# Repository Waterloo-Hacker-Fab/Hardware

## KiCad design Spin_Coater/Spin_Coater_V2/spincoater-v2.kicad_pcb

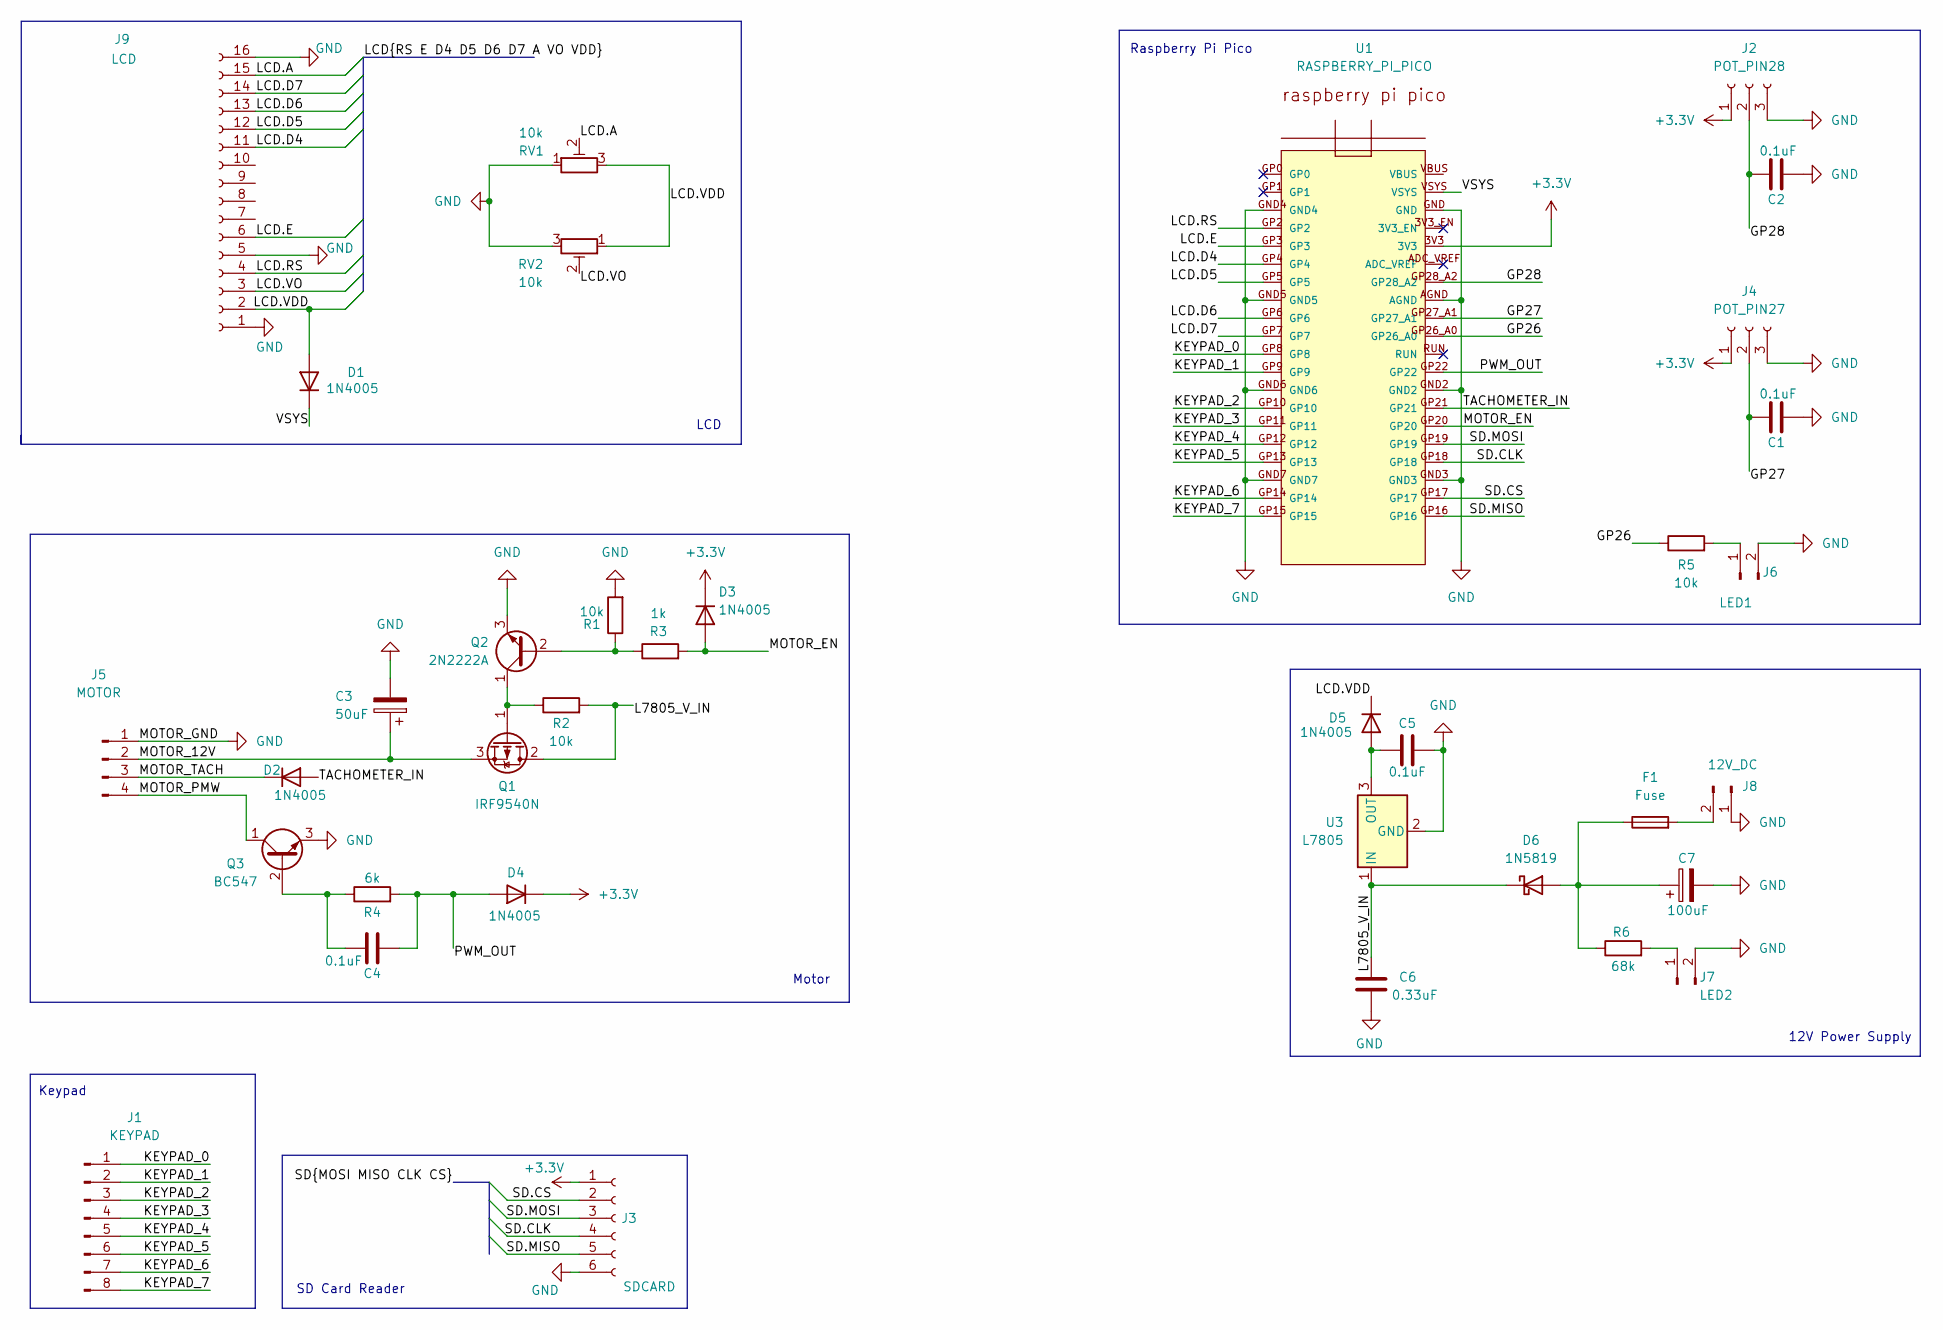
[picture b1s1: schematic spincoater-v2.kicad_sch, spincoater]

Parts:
C1, C2, C4, C5: 0.1uF; C_0603_1608Metric_Pad1.08x0.95mm_HandSolder
C3: 50uF; CP_Radial_D13.0mm_P5.00mm
C6: 0.33uF; C_0603_1608Metric_Pad1.08x0.95mm_HandSolder
C7: 100uF; CP_Radial_D13.0mm_P5.00mm
D1, D2, D3, D4, D5: 1N4005; D_DO-41_SOD81_P10.16mm_Horizontal
D6: 1N5819; D_DO-41_SOD81_P10.16mm_Horizontal
F1: Fuse; Fuseholder_Keystone_3555-2
J1: KEYPAD; PinSocket_1x08_P2.54mm_Vertical
J2: POT_PIN28; PinSocket_1x03_P2.54mm_Vertical
J3: SDCARD; PinSocket_1x06_P2.54mm_Vertical
J4: POT_PIN27; PinSocket_1x03_P2.54mm_Vertical
J5: MOTOR; PinHeader_1x04_P2.54mm_Vertical
J6: LED1; PinHeader_1x02_P2.54mm_Vertical
J7: LED2; PinHeader_1x02_P2.54mm_Vertical
J8: 12V_DC; PinHeader_1x02_P2.54mm_Vertical
J9: LCD; PinSocket_1x16_P2.54mm_Vertical
Q1: IRF9540N; TO-220-3_Horizontal_TabUp
Q2: 2N2222A; TO-92_Inline_Horizontal1
Q3: BC547; TO-92_Inline_Horizontal1
R1, R2, R5: 10k; R_0603_1608Metric_Pad0.98x0.95mm_HandSolder
R3: 1k; R_0603_1608Metric_Pad0.98x0.95mm_HandSolder
R4: 6k; R_0603_1608Metric_Pad0.98x0.95mm_HandSolder
R6: 68k; R_0603_1608Metric_Pad0.98x0.95mm_HandSolder
RV1, RV2: 10k; Potentiometer_Vishay_T93YA_Vertical
U1: RASPBERRY_PI_PICO; RPI_PICO
U3: L7805; TO-220-3_Horizontal_TabUp

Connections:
+3.3V: D3.1 (K), D4.1 (K), J2.1, J3.1, J4.1, U1.3V3
/GP26: R5.1, U1.GP26_A0
/GP27: C1.1, J4.2, U1.GP27_A1
/GP28: C2.1, J2.2, U1.GP28_A2
/KEYPAD_0: J1.1, U1.GP8
/KEYPAD_1: J1.2, U1.GP9
/KEYPAD_2: J1.3, U1.GP10
/KEYPAD_3: J1.4, U1.GP11
/KEYPAD_4: J1.5, U1.GP12
/KEYPAD_5: J1.6, U1.GP13
/KEYPAD_6: J1.7, U1.GP14
/KEYPAD_7: J1.8, U1.GP15
/L7805_V_IN: C6.2, D6.1 (K), Q1.2 (D), R2.2, U3.1 (IN)
/LCD.A: J9.15, RV1.2
/LCD.D4: J9.11, U1.GP4
/LCD.D5: J9.12, U1.GP5
/LCD.D6: J9.13, U1.GP6
/LCD.D7: J9.14, U1.GP7
/LCD.E: J9.6, U1.GP3
/LCD.RS: J9.4, U1.GP2
/LCD.VDD: D1.2 (A), D5.1 (K), J9.2, RV1.3, RV2.1
/LCD.VO: J9.3, RV2.2
/MOTOR_12V: C3.1, J5.2, Q1.3 (S)
/MOTOR_EN: D3.2 (A), R3.2, U1.GP20
/MOTOR_PMW: J5.4, Q3.1 (C)
/MOTOR_TACH: D2.1 (K), J5.3
/PWM_OUT: C4.2, D4.2 (A), R4.2, U1.GP22
/SD.CLK: J3.4, U1.GP18
/SD.CS: J3.2, U1.GP17
/SD.MISO: J3.5, U1.GP16
/SD.MOSI: J3.3, U1.GP19
/TACHOMETER_IN: D2.2 (A), U1.GP21
/VSYS: D1.1 (K), U1.VSYS
GND: C1.2, C2.2, C3.2, C5.2, C6.1, C7.2, J2.3, J3.6, J4.3, J5.1, J6.2, J7.2, J8.1, J9.1, J9.5, J9.16, Q2.3 (E), Q3.3 (E), R1.2, RV1.1, RV2.3, U1.AGND, U1.GND, U1.GND2, U1.GND3, U1.GND4, U1.GND5, U1.GND6, U1.GND7, U3.2 (GND)
unnamed: C5.1, D5.2 (A), U3.3 (OUT)
unnamed: C7.1, D6.2 (A), F1.1, R6.1
unnamed: J6.1, R5.2
unnamed: J7.1, R6.2
unnamed: F1.2, J8.2
unnamed: Q1.1 (G), Q2.1 (C), R2.1
unnamed: Q2.2 (B), R1.1, R3.1
unnamed: C4.1, Q3.2 (B), R4.1

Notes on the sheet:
Keypad
SD Card Reader
Motor
LCD
12V Power Supply
Raspberry Pi Pico

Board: 2 copper layers, 36 parts (0 on the bottom side), 42 nets, no tracks yet.

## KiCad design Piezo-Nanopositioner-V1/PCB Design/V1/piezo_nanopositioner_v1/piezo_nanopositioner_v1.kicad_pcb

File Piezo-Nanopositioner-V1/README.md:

# Piezo Stage 

## Overview
This is an open source piezo stage build, heavily inspired by the following paper: https://www.sciencedirect.com/science/article/pii/S2468067222000621

Notes about the paper mentioned above: 
1. The paper provides a great schematic for a piezo driver PCB. However, some of the parts are obsolete, and the design is built on a perfboard.

2. The paper also includes CAD design files. However, the mechanical parts used in these designs are either difficult to source or obsolete. In our design, we decided to replace these hard-to-get parts with alternatives based on CMU’s current stage. The CAD files require no modification when used with the current BOM.

The goal of the PCB redesign was to: 
1. Remove obsolete components -  Easier to source parts and ensures long-term availability.

2. Remove perfboard design - Simplifies the assembly process.

The goal of the CAD redesign was to: 
1. Modular attachment system - Allows mounting the stage to various surfaces (e.g., metric/imperial optical breadboard).

2. Modular mounting surface - Enables testing of different wafer clamping systems.

3. Up-to-date 3D printable CAD files - No obsolete parts, uses current BOM

4. Provide a "standard" stage - Provide a "base" so people can build on top of (incorporating measurement systems or custom wafer clamps.).

5. Provide a cheaper alternative for building a piezo stage.

---

## Folder Structure

- **/CAD Design/**  
  Contains all the .sldprt/.sldasm/.stl files needed to print/modify for your needs.  
  <span style="color:red"> Note: Contains BOM for the piezo stage build ("MECH_piezo_stage_BOM.xlsx") </span>

- **/LTspice Simulation/**  
  Nitty gritty simulations of schematics (good for learning, useless for recreating the project).

- **/PCB Design/**  
  PCB design files (Gerber and drill files) for the XYZ Piezo Stage driver. Also comes with KiCAD files.  
  <span style="color:red"> Note: Contains BOM for the piezo stage PCB ("PCB_piezo_stage_BOM.csv") </span>

- **/Pictures/**  
  Pictures of the PCB and mechanical parts.

- **/Firmware/**  
  Coming soon.

---

## 3D Printing

- List of parts to print (Check "Printed Parts" folder):  
  - `XY_Base.SLDPRT` — Base frame for both X & Y stage (Print 2 for XY stage.)  
  - `XY_Plate.SLDPRT` — Top plate for both X & Y stage (Print 2 for XY stage.)
  - `Z_Base.SLDPRT` — Base frame for Z stage (print only 1 for XYZ stage.)  
  - `Z_Plate.SLDPRT` — Top plate for Z stage (print only 1 for XYZ stage.)
  - `Z_Cover.SLDPRT` — Side cover frame for Z stage (print only 1 for XYZ stage.)

  Optional:
  - `XY_Base_Connector_(Metric).SLDPRT` — Connector for mounting the stage to a metric optical breadboard (print only 1.)
  - `XY_Base_Connector_(Imperial).SLDPRT` — Coming soon.

- Printing recommendations:  
  - Material: PLA or ABS  
  - Layer height: 0.2 mm  
  - Infill: 20% (adjust for strength as needed)  
  - Supports: Required for all parts.

---

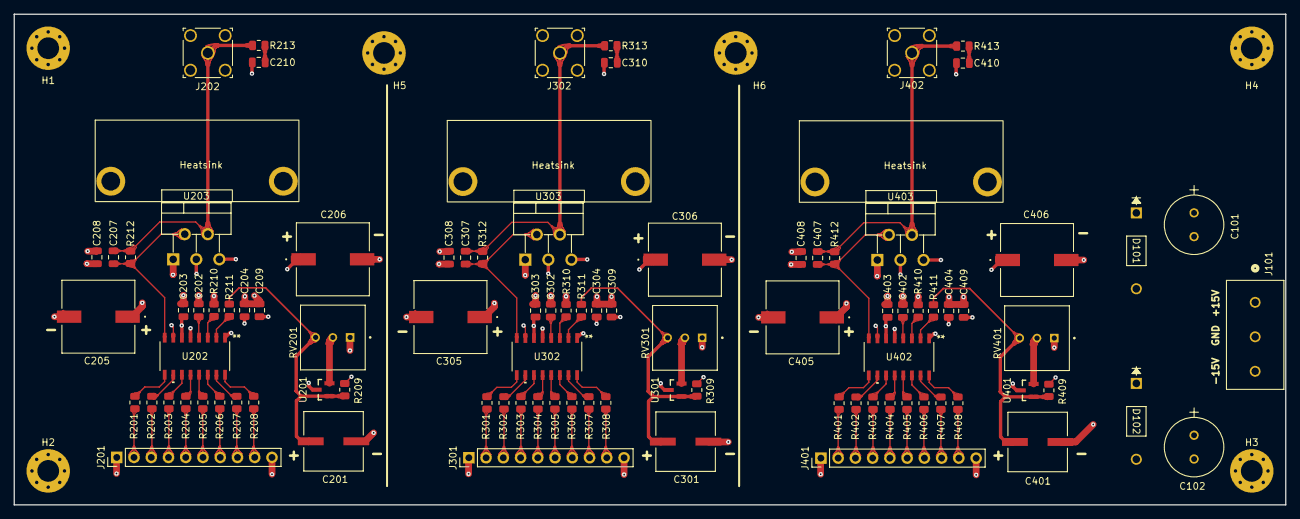
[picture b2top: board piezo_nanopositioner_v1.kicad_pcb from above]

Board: 4 copper layers, 187.2 x 72.2 mm, 101 parts (0 on the bottom side), 27 nets.

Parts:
C101, C102: 100uF 50V; CAP_YX_8X11P5_RUB
C201, C301, C401: 47u; CAP_EEFC_E_PAN
C202, C302, C402: 10n; C_0805_2012Metric
C203, C204, C208, C209, C303, C304, C308, C309, C403, C404, C408, C409: 100n; C_0805_2012Metric
C205, C206, C305, C306, C405, C406: 470u; CAP_ZSU_G12_PAN
C207, C307, C407: 68p; C_0805_2012Metric
C210, C310, C410: 4.7n; C_0805_2012Metric
D101, D102: D; DO-41_DIO
H1, H2, H3, H4, H5, H6: MountingHole; MountingHole_3.2mm_M3_Pad_Via
Heatsink: V6560Y
Heatsink#2, Heatsink#3: V6560Y
J101: Conn_01x03_Pin; CONN_39880-0303_MOL
J201, J301, J401: Conn_01x10_Pin; PinHeader_1x10_P2.54mm_Vertical
J202, J302, J402: RF2-04A-T-00-50-G; CONN_RF2-04A-T-00-50-G_ADM
R201, R202, R203, R204, R205, R206, R207, R208, R301, R302, R303, R304, R305, R306, R307, R308, R401, R402, R403, R404, R405, R406, R407, R408: 100R; R_0805_2012Metric
R209, R309, R409: 1k; R_0805_2012Metric
R210, R211, R310, R311, R410, R411: 5k; R_0805_2012Metric
R212, R312, R412: 15k; R_0805_2012Metric
R213, R313, R413: 10R; R_0805_2012Metric
RV201, RV301, RV401: 10k; TRIM_COM-09806
U201, U301, U401: TL431AIDBZR; DBZ0003A_N
U202, U302, U402: DAC0800LCM; M16A_TEX
U203, U303, U403: TDA2050; TO-220-5_P3.4x3.7mm_StaggerOdd_Lead3.8mm_Vertical

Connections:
+15V: C101.1, C204.2, C206.1, C209.1, C304.2, C306.1, C309.1, C404.2, C406.1, C409.1, D101.1 (K), J101.1, R209.1, R309.1, R409.1, U202.1 (V+), U203.5 (+Vs), U302.1 (V+), U303.5 (+Vs), U402.1 (V+), U403.5 (+Vs)
-15V: C102.2, C202.2, C203.1, C205.2, C208.2, C302.2, C303.1, C305.2, C308.2, C402.2, C403.1, C405.2, C408.2, D102.2 (A), J101.3, U202.7 (V-), U203.3 (-Vs), U302.7 (V-), U303.3 (-Vs), U402.7 (V-), U403.3 (-Vs)
/Z_DAC/VRef+: C201.1, C301.1, C401.1, R209.2, R211.2, R309.2, R311.2, R409.2, R411.2, RV201.3, RV301.3, RV401.3, U201.1 (c), U301.1 (c), U401.1 (c)
GND: C101.2, C102.1, C201.2, C203.2, C204.1, C205.1, C206.2, C208.1, C209.2, C210.2, C301.2, C303.2, C304.1, C305.1, C306.2, C308.1, C309.2, C310.2, C401.2, C403.2, C404.1, C405.1, C406.2, C408.1, C409.2, C410.2, D101.2 (A), D102.1 (K), J101.2, J201.1, J201.10, J202.2, J202.3, J202.4, J202.5, J301.1, J301.10, J302.2, J302.3, J302.4, J302.5, J401.1, J401.10, J402.2, J402.3, J402.4, J402.5, R210.2, R310.2, R410.2, RV201.1, RV301.1, RV401.1, U201.3 (a), U202.5 (VLC), U202.6 (~IOUT), U203.1 (+), U301.3 (a), U302.5 (VLC), U302.6 (~IOUT), U303.1 (+), U401.3 (a), U402.5 (VLC), U402.6 (~IOUT), U403.1 (+)
unnamed: C210.1, C310.1, C410.1, R213.2, R313.2, R413.2
unnamed: J201.2, J301.2, J401.2, R201.1, R301.1, R401.1
unnamed: J201.3, J301.3, J401.3, R202.1, R302.1, R402.1
unnamed: J201.4, J301.4, J401.4, R203.1, R303.1, R403.1
unnamed: J201.5, J301.5, J401.5, R204.1, R304.1, R404.1
unnamed: J201.6, J301.6, J401.6, R205.1, R305.1, R405.1
unnamed: J201.7, J301.7, J401.7, R206.1, R306.1, R406.1
unnamed: J201.8, J301.8, J401.8, R207.1, R307.1, R407.1
unnamed: J201.9, J301.9, J401.9, R208.1, R308.1, R408.1
unnamed: C207.2, C307.2, C407.2, J202.1 (Sig), J302.1 (Sig), J402.1 (Sig), R212.2, R213.1, R312.2, R313.1, R412.2, R413.1, U203.4, U303.4, U403.4
unnamed: RV201.2, RV301.2, RV401.2, U201.2 (REF), U301.2 (REF), U401.2 (REF)
unnamed: R201.2, R301.2, R401.2, U202.9 (B1), U302.9 (B1), U402.9 (B1)
unnamed: R202.2, R302.2, R402.2, U202.10 (B2), U302.10 (B2), U402.10 (B2)
unnamed: R203.2, R303.2, R403.2, U202.11 (B3), U302.11 (B3), U402.11 (B3)
unnamed: R204.2, R304.2, R404.2, U202.12 (B4), U302.12 (B4), U402.12 (B4)
unnamed: R205.2, R305.2, R405.2, U202.13 (B5), U302.13 (B5), U402.13 (B5)
unnamed: R206.2, R306.2, R406.2, U202.14 (B6), U302.14 (B6), U402.14 (B6)
unnamed: R207.2, R307.2, R407.2, U202.15 (B7), U302.15 (B7), U402.15 (B7)
unnamed: R208.2, R308.2, R408.2, U202.16 (B8), U302.16 (B8), U402.16 (B8)
unnamed: C202.1, C302.1, C402.1, U202.4 (COMP), U302.4 (COMP), U402.4 (COMP)
unnamed: C207.1, C307.1, C407.1, R212.1, R312.1, R412.1, U202.8 (IOUT), U203.2 (-), U302.8 (IOUT), U303.2 (-), U402.8 (IOUT), U403.2 (-)
unnamed: R211.1, R311.1, R411.1, U202.2 (VREF(+)), U302.2 (VREF(+)), U402.2 (VREF(+))
unnamed: R210.1, R310.1, R410.1, U202.3 (VREF(-)), U302.3 (VREF(-)), U402.3 (VREF(-))

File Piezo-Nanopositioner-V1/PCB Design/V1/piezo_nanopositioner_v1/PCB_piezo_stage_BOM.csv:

Reference,Value,Datasheet,Footprint,Qty,DNP,Manufacturer,Manufacturer Part,Distributor Link
"J202,J302,J402",RF2-04A-T-00-50-G,RF2-04A-T-00-50-G,CONN_RF2-04A-T-00-50-G_ADM,3,,Adam Tech ,RF2-04A-T-00-50-G ,https://www.digikey.ca/en/products/detail/adam-tech/RF2-04A-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 
"HS1,HS2,HS3",Heatsink,~,V6560Y:V6560Y,3,,Assmann WSW Components,V6560Y,https://www.digikey.ca/en/products/detail/assmann-wsw-compon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
"R209,R309,R409",1k,~,Resistor_SMD:R_0805_2012Metric,3,,Bourns Inc. ,CR0805-JW-102ELF ,https://www.digikey.ca/en/products/detail/bourns-inc/CR0805-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 
"R213,R313,R413",10R,~,Resistor_SMD:R_0805_2012Metric,3,,Bourns Inc. ,CR0805AFX-10R0EAS ,https://www.digikey.ca/en/products/detail/bourns-inc/CR0805A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 
"J201,J301,J401",Conn_01x10_Pin,~,Connector_PinHeader_2.54mm:PinHeader_1x10_P2.54mm_Vertical,3,,Harwin Inc. ,M22-2511005 ,https://www.digikey.ca/en/products/detail/harwin-inc/M22-251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 
"C202,C302,C402",10n,~,Capacitor_SMD:C_0805_2012Metric,3,,KEMET ,C0805C103F5GECAUTO ,https://www.digikey.ca/en/products/detail/kemet/C0805C103F5G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 
"C203,C204,C208,C209,C303,C304,C308,C309,C403,C404,C408,C409",100n,~,Capacitor_SMD:C_0805_2012Metric,12,,KEMET ,C0805C104K5RACTU ,https://www.digikey.ca/en/products/detail/kemet/C0805C104K5R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 
"C210,C310,C410",4.7n,~,Capacitor_SMD:C_0805_2012Metric,3,,KEMET ,C0805C472KDRACAUTO ,https://www.digikey.ca/en/products/detail/kemet/C0805C472KDR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 
"C207,C307,C407",68p,~,Capacitor_SMD:C_0805_2012Metric,3,,KEMET ,C0805C680K5GACTU ,https://www.digikey.ca/en/products/detail/kemet/C0805C680K5G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 
"D101,D102",D,~,Diode_THT:DO-41_DIO,2,,onsemi ,1N4001RLG ,https://www.digikey.ca/en/products/detail/onsemi/1N4001RLG/917621 
"C201,C301,C401",47u,~,Capacitor_SMD:CAP_EEFC_E_PAN,3,,Panasonic Electronic Components,EEE-FC1E470P,https://www.digikey.ca/en/products/detail/panasonic-electron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
"C205,C206,C305,C306,C405,C406",470u,~,Capacitor_THT:CAP_ZSU_G12_PAN,6,,Panasonic Electronic Components ,EEH-ZS1E471P ,https://www.digikey.ca/en/products/detail/panasonic-electron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 
"R212,R312,R412",15k,~,Resistor_SMD:R_0805_2012Metric,3,,Rohm Semiconductor ,ESR10EZPJ153 ,https://www.digikey.ca/en/products/detail/rohm-semiconductor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 
"C101,C102",100uF 50V,50YXJ100MT78X11.5,Capacitor_THT:CAP_YX_8X11P5_RUB,2,,Rubycon,50YXJ100MT78X11.5,https://www.digikey.ca/en/products/detail/rubycon/50YXJ100MT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
"RV201,RV301,RV401",10k,~,Potentiometer_THT:TRIM_COM-09806,3,,SparkFun Electronics ,COM-09806 ,https://www.digikey.ca/en/products/detail/sparkfun-electroni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 
"R210,R211,R310,R311,R410,R411",5k,~,Resistor_SMD:R_0805_2012Metric,6,,TE Connectivity Passive Product ,RLC73K2A1R0FTD ,https://www.digikey.ca/en/products/detail/te-connectivity-pa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 
"U202,U302,U402",DAC0800LCM,DAC0800LCM,M16A_TEX,3,,Texas Instruments ,DAC0800LCM/NOPB ,https://www.digikey.ca/en/products/detail/texas-instruments/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 
"U201,U301,U401",TL431AIDBZR,TL431AIDBZR,DBZ0003A_N,3,,Texas Instruments ,TL431AIDBZR ,https://www.digikey.ca/en/products/detail/texas-instruments/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 
"R201,R202,R203,R204,R205,R206,R207,R208,R301,R302,R303,R304,R305,R306,R307,R308,R401,R402,R403,R404,R405,R406,R407,R408",100R,~,Resistor_SMD:R_0805_2012Metric,24,,Vishay Dale,CRCW0805100RJNEC ,https://www.digikey.ca/en/products/detail/vishay-dale/CRCW08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 
J101,Conn_01x03_Pin,~,CONN_39880-0303_MOL,1,,Molex,398800303,https://www.digikey.ca/en/products/detail/molex/0398800303/2741452
"U203,U303,U403",LM1857 ,~,Package_TO_SOT_THT:TO-220-5_P3.4x3.7mm_StaggerOdd_Lead3.8mm_Vertical,3,,Texas Instruments ,LM1875T/NOPB ,https://www.digikey.com/en/products/detail/texas-instruments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

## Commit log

2024-10-02 add: finished MCU schematic labels
2024-10-18 Add files via upload
    The schematic and software for the tube furnace.
    Software:
    The software for now only contains the basic setup including encoder debouncing, LED test, and I2C communication with the LCD. The encoder debouncing and LED test were done through timer interrupts.
    Schematic:
    Mostly self-explanatory. The data logger fits on top of the Arduino and the outlets on the data logger are soldered to the corresponding pins on the Arduino. There is no schematic for the plug and fu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
2024-10-18 Create Tube Furnace
2024-10-19 Tube Furnace Schematic and Software
    Schematic:
    Pretty self-explanatory. The data logger is supposed to fit onto the Arduino. The outlets soldered onto the data logger are also soldered to the corresponding pins on the Arduino. No schematic for th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
    Code:
    Basic setup code. Includes: LED test, encoder debouncing, and I2C communication with the LCD and encoder. The LED test and encoder debounce were done through timer interrupts.
2024-11-30 test
2024-12-08 V1 schematic design of the spincoater completed.
2024-12-08 small trace fix
2024-12-10 added footprints to most of the components, still need to add pico footprint, and modify some of the resistor fingerprints 68k and 6k not common res vals. Also change some of the 10k resistor footpri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
2024-12-10 made some final changes to schematic and the fingerprints, might still need to change a few polarized caps
2024-12-10 started the pcb design, still very messy, look into using the autorouter package for help
2024-12-11 Organized the pcb layout a bit, not sure if it is ideal. Ran the PCB through auto routing. Changed transistors to horizontal orrientation so that we can attach the LCD screen directly to the PCB. The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
2024-12-17 added mounting holes for pcb, made it 2.6mm radius
2024-12-17 changed mounting hole radius size to 2mm
2025-01-16 fixed trace issue
2025-01-20 Finished creating LTspice simulation for spincoater V1. Ensured that LCD potentiometer does not overdrive the LCD. Tested motor power supply circuit for stable voltage. Tested LCD power supply. Teste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
2025-01-21 simplified schematic.
2025-01-22 added silkscreen, fixed RPi Pico position on PCB.
2025-01-22 V2 version of spincoater PCB. Changed the footprints of the pot's, changed layout of the PCB (will fit in the box created in the vid). Still need to finish more of layout and change more footprints, 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
2025-01-22 Organizing the project folder...
2025-01-22 deleting a folder from repo cuz I made a copy.
2025-01-22 removed duplicate fldr
2025-01-22 added folder including annotated schematics.
2025-01-23 Created rough layout for new version of PCB. Fits in required space.
2025-01-29 Almost finished schematic of the piezo stage.
2025-01-29 finalized schematic, added hierarchical sheets for X,Y,Z circuit. Added all part fingerprints.
2025-01-29 cleaning up the repo...
2025-01-29 added gitignore for .lck files, fp-info-cache , auto_saved_files
2025-01-29 changed /fp-info-cache/ to fp-info-cache in gitignore
2025-01-30 started PCB design, almost finished first DAC.
2025-01-30 Created rough PCB component layout for Z actuator.
2025-02-12 added heatsink to XYZ schematics, finalized BOM, minimal PCB layout done.
2025-02-16 created circuit for voltage regulator, not exactly sure why it is behaving that way however, but it should work irl.
2025-02-16 explained what Vref does for the TL431 and DAC0800 circuit.
2025-02-19 started working on op-amp simulation. The non-inverting part of the op-amp makes sense and works, still need to do some investigation about the zobel network.
2025-02-19 almost finished LTspice simulation, still want to test out the voltage input vs output.
2025-02-26 op amp model in LTspice finally working as intended. Fix was done to reverse the current of the DAC because thats how it is in the datasheet. Op-amp is in transimped. config. and also acts like a low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
2025-02-28 added pics of op-amp circuit analyzed. Split it between transimpendance and Zobel network.
2025-03-30 finished routing the traces, added teardrops to traces.
2025-04-06 started placing vias, created +/-15V zones. Created ground plane on second layer.
2025-04-19 Added 3d model files for component. Finished connecting the fill zones. Added mounting holes. Added pictures of pcb and layout.
2025-04-19 updated layout pic
2025-04-19 updated layout img
2025-04-20 added GND,+/-15V to silkscreen.
2025-04-20 deleted unused files
2025-04-20 Fixed ground plane issue (ground loop found). Solution was to move from a 2 layer PCB to 4 layer PCB. Will cost extra but signal integrity will benefit.
2025-05-03 added gerber and drill files.
2025-06-06 CAD design for piezo stage complete. Assemblies complete.
2025-06-06 added README file, describing project, file locations, etc.
2025-06-06 added some pics from CAD assembly.
2025-06-10 renamed BOM for simiplicity. There will be seperate BOM's for the PCB, MECH, etc
2025-06-11 added info to CAD_BOM, added info to README.
2025-06-11 changed file name for mech BOM
2025-06-11 included section for XYZ and XY in BOM, incase people want to make only XY stages.
2025-06-12 updated README to emphasize the 2 BOM's (Mech and PCB).
2025-07-28 added much needed polarity markings on silkscreen. Added testing rig files for testing your piezo element, clamps down the piezo and reads accelerometer data & temperatre (thermistor). Also added fir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
2025-08-30 Rename project folder to Spin_Coater
2025-08-30 files reorg
2025-09-01 Added interferometer project, recorded some simulation stats in README file
2025-09-01 corrected readme file
